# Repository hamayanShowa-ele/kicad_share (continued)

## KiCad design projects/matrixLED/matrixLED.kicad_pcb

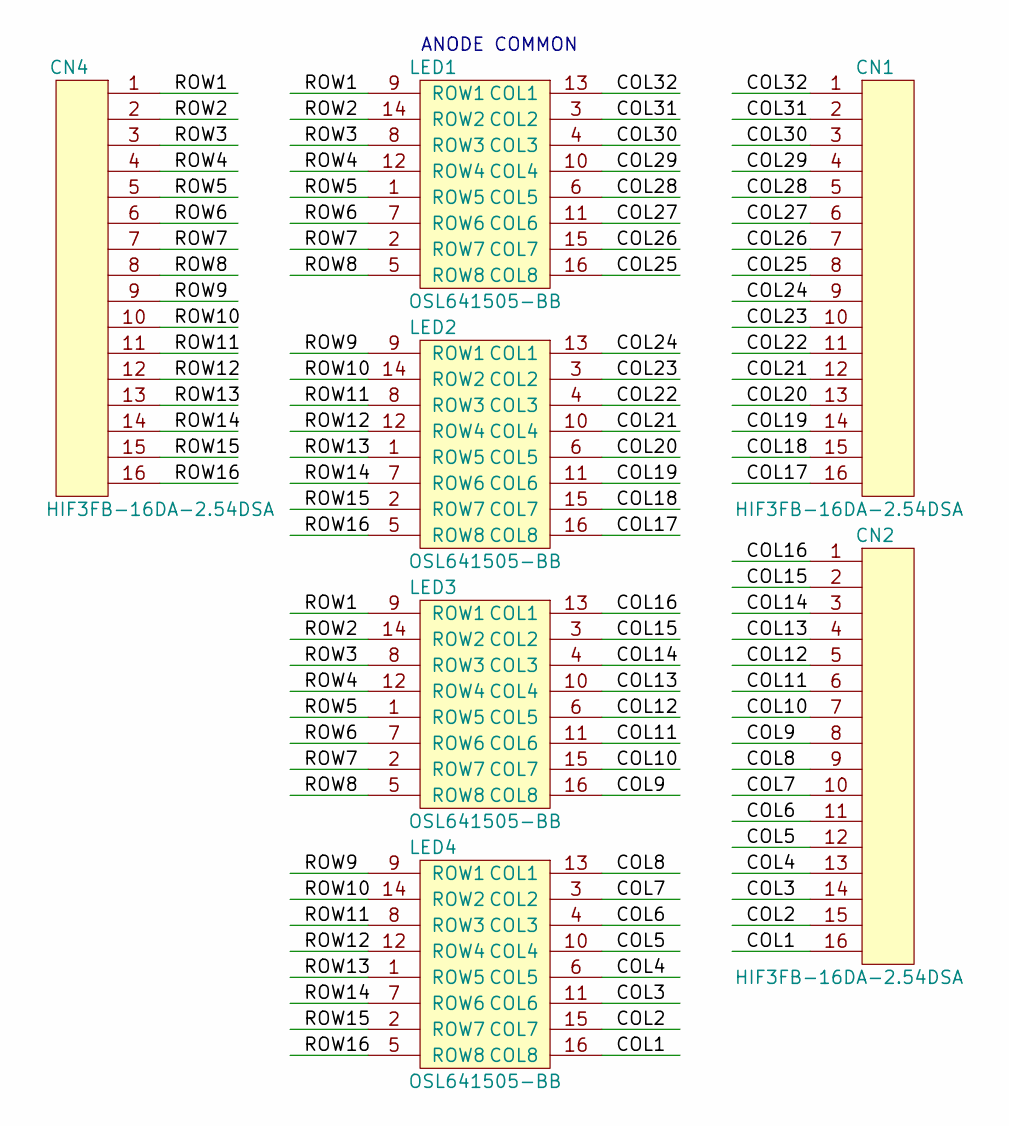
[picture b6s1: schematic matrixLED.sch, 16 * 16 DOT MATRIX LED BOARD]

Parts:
CN1, CN2, CN4: HIF3FB-16DA-2.54DSA; cn_HIF3FC-16PA-254DSA
LED1, LED2, LED3, LED4: OSL641505-BB; led_OSL641505

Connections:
/COL1: CN2.16, LED4.16 (COL8)
/COL2: CN2.15, LED4.15 (COL7)
/COL3: CN2.14, LED4.11 (COL6)
/COL4: CN2.13, LED4.6 (COL5)
/COL5: CN2.12, LED4.10 (COL4)
/COL6: CN2.11, LED4.4 (COL3)
/COL7: CN2.10, LED4.3 (COL2)
/COL8: CN2.9, LED4.13 (COL1)
/COL9: CN2.8, LED3.16 (COL8)
/COL10: CN2.7, LED3.15 (COL7)
/COL11: CN2.6, LED3.11 (COL6)
/COL12: CN2.5, LED3.6 (COL5)
/COL13: CN2.4, LED3.10 (COL4)
/COL14: CN2.3, LED3.4 (COL3)
/COL15: CN2.2, LED3.3 (COL2)
/COL16: CN2.1, LED3.13 (COL1)
/COL17: CN1.16, LED2.16 (COL8)
/COL18: CN1.15, LED2.15 (COL7)
/COL19: CN1.14, LED2.11 (COL6)
/COL20: CN1.13, LED2.6 (COL5)
/COL21: CN1.12, LED2.10 (COL4)
/COL22: CN1.11, LED2.4 (COL3)
/COL23: CN1.10, LED2.3 (COL2)
/COL24: CN1.9, LED2.13 (COL1)
/COL25: CN1.8, LED1.16 (COL8)
/COL26: CN1.7, LED1.15 (COL7)
/COL27: CN1.6, LED1.11 (COL6)
/COL28: CN1.5, LED1.6 (COL5)
/COL29: CN1.4, LED1.10 (COL4)
/COL30: CN1.3, LED1.4 (COL3)
/COL31: CN1.2, LED1.3 (COL2)
/COL32: CN1.1, LED1.13 (COL1)
/ROW1: CN4.1, LED1.9 (ROW1), LED3.9 (ROW1)
/ROW2: CN4.2, LED1.14 (ROW2), LED3.14 (ROW2)
/ROW3: CN4.3, LED1.8 (ROW3), LED3.8 (ROW3)
/ROW4: CN4.4, LED1.12 (ROW4), LED3.12 (ROW4)
/ROW5: CN4.5, LED1.1 (ROW5), LED3.1 (ROW5)
/ROW6: CN4.6, LED1.7 (ROW6), LED3.7 (ROW6)
/ROW7: CN4.7, LED1.2 (ROW7), LED3.2 (ROW7)
/ROW8: CN4.8, LED1.5 (ROW8), LED3.5 (ROW8)
/ROW9: CN4.9, LED2.9 (ROW1), LED4.9 (ROW1)
/ROW10: CN4.10, LED2.14 (ROW2), LED4.14 (ROW2)
/ROW11: CN4.11, LED2.8 (ROW3), LED4.8 (ROW3)
/ROW12: CN4.12, LED2.12 (ROW4), LED4.12 (ROW4)
/ROW13: CN4.13, LED2.1 (ROW5), LED4.1 (ROW5)
/ROW14: CN4.14, LED2.7 (ROW6), LED4.7 (ROW6)
/ROW15: CN4.15, LED2.2 (ROW7), LED4.2 (ROW7)
/ROW16: CN4.16, LED2.5 (ROW8), LED4.5 (ROW8)

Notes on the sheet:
ANODE COMMON

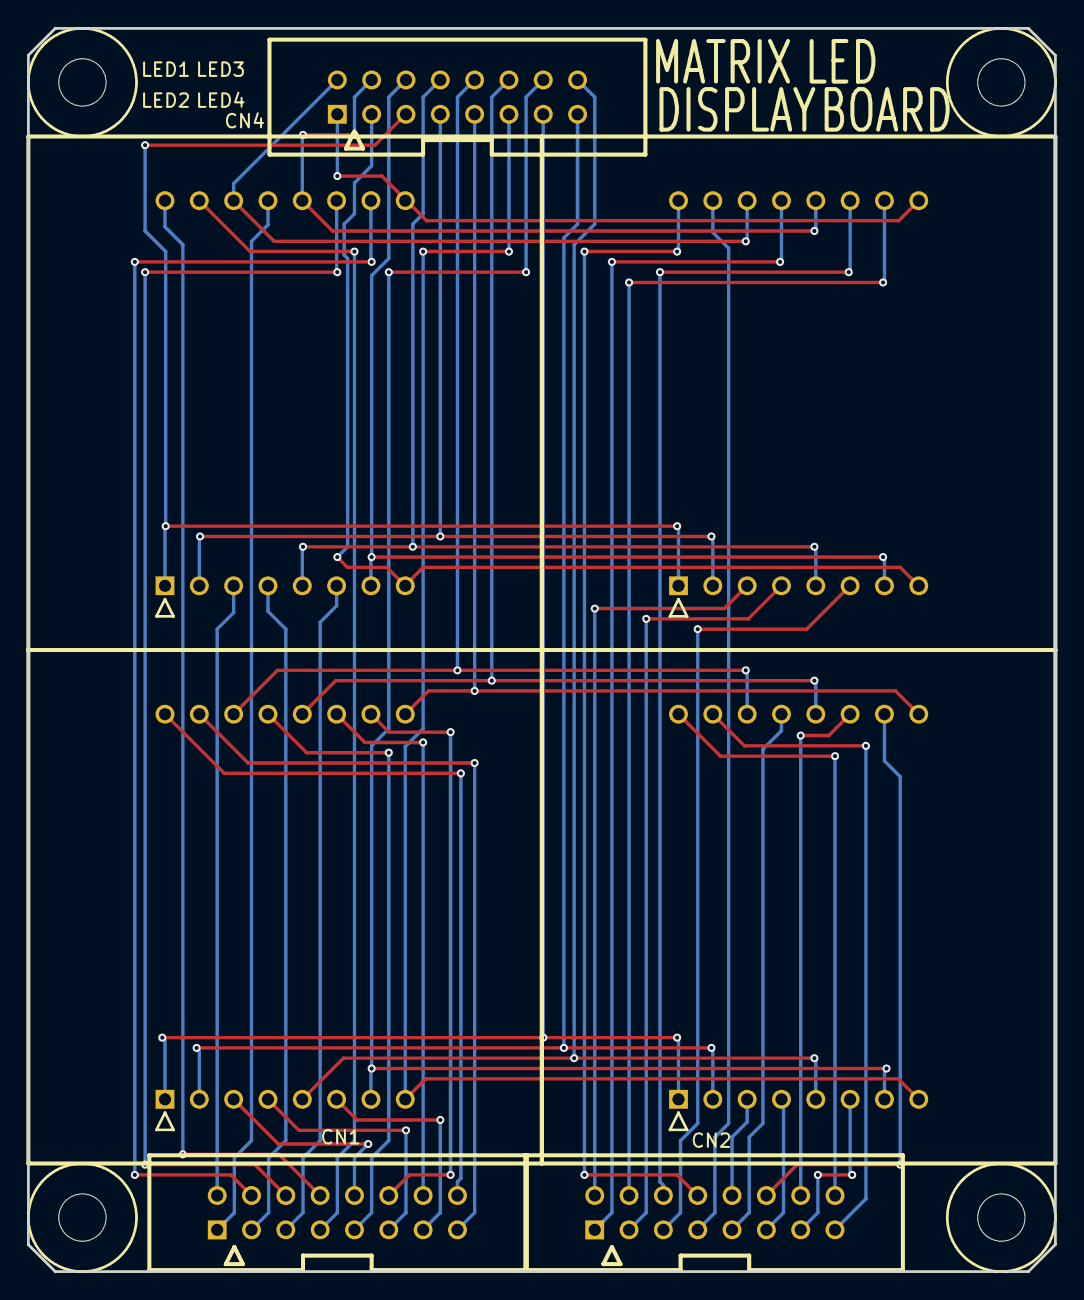
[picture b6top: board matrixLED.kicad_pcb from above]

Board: 2 copper layers, 76.0 x 92.0 mm, 7 parts (0 on the bottom side), 48 nets.

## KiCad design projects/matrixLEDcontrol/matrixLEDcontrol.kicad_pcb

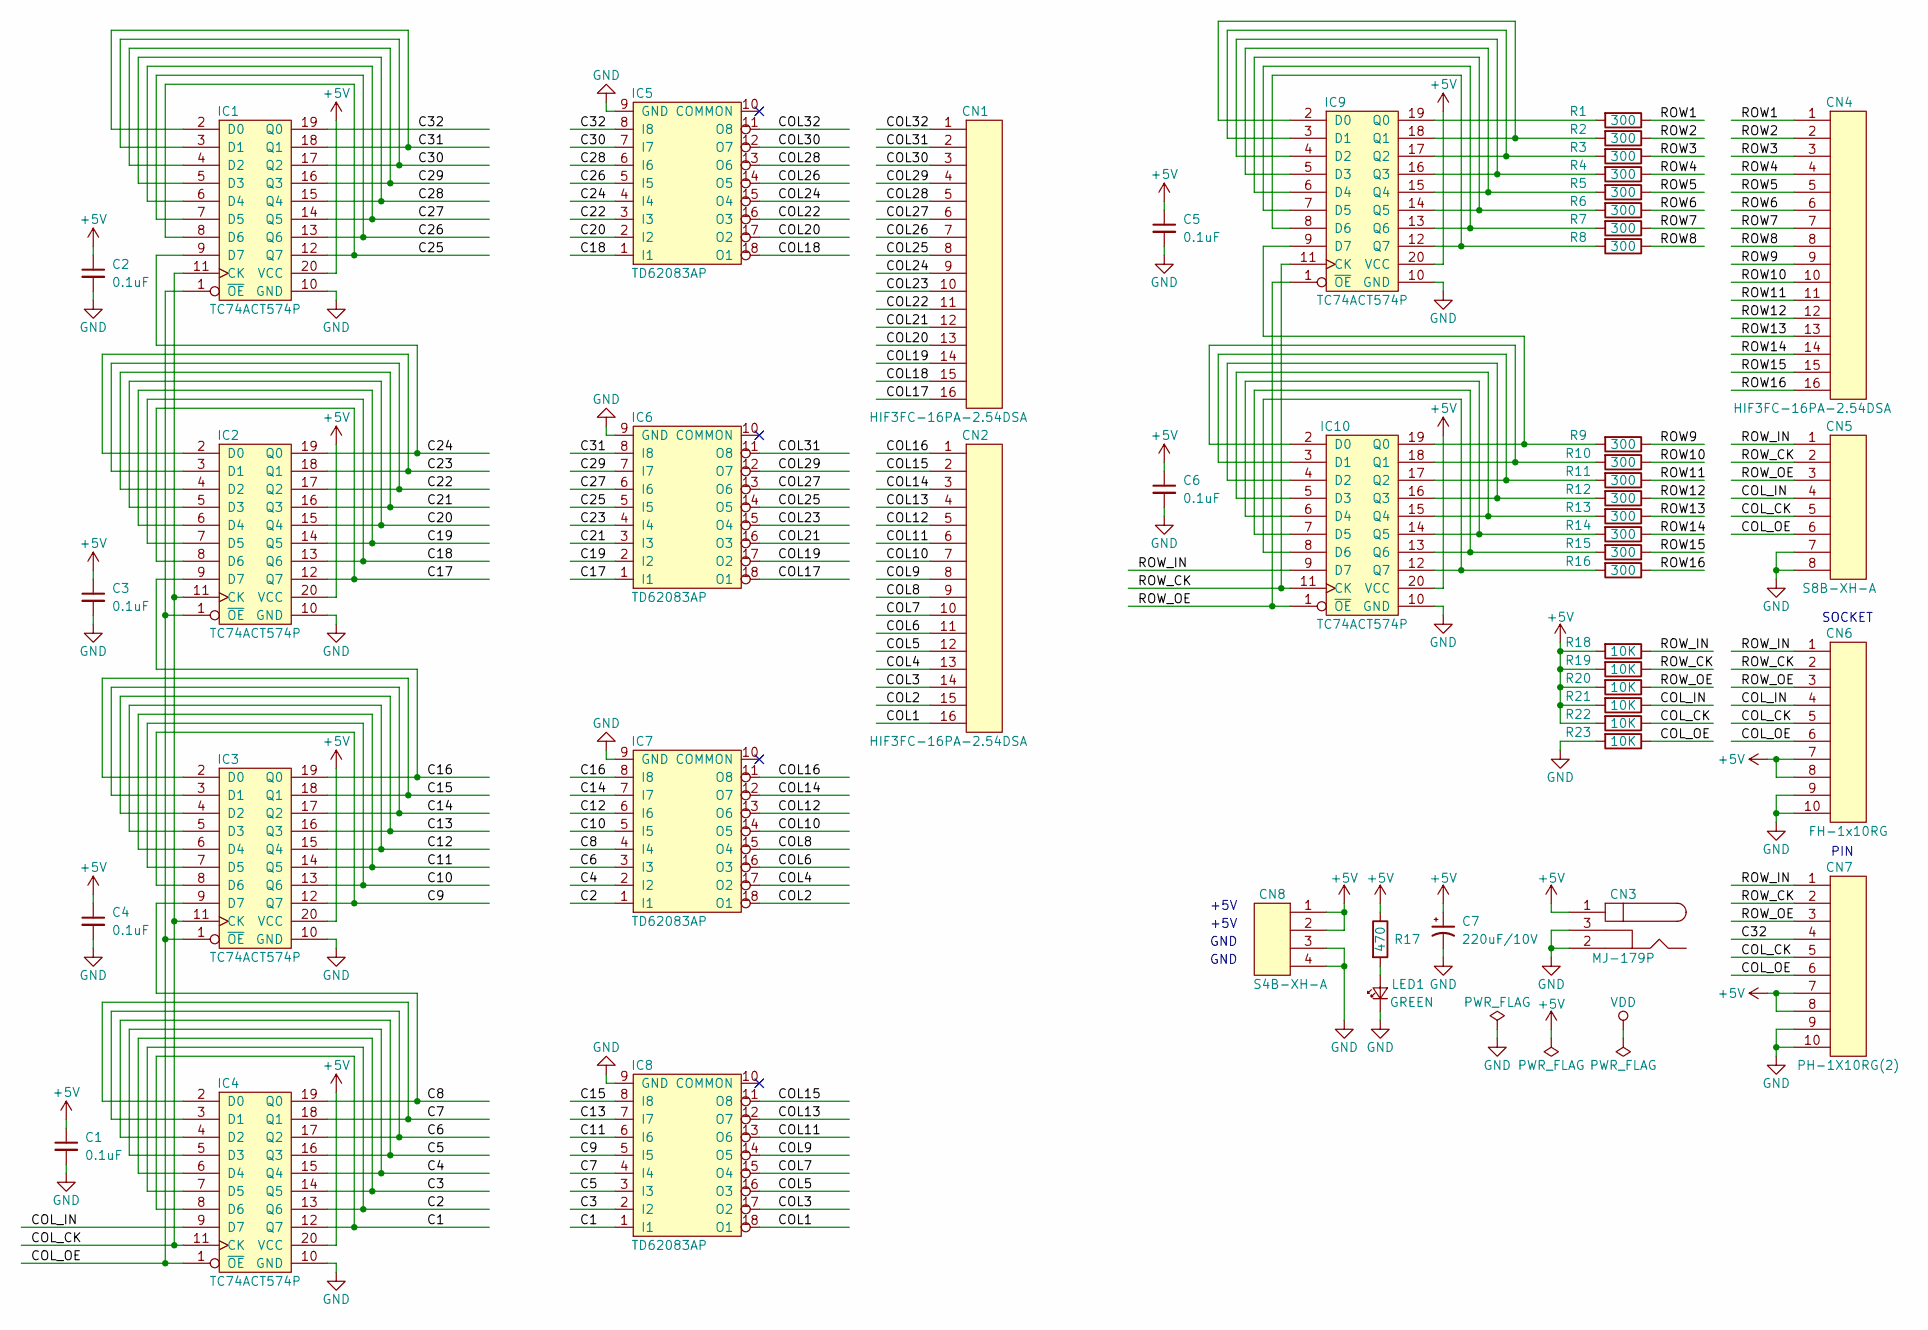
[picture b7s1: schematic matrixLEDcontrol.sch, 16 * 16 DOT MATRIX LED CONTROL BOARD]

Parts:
C1, C2, C3, C4, C5, C6: 0.1uF; C_0805
C7: 220uF/10V; CP_Radial_D8.25mm_P3.80mm
CN1, CN2, CN4: HIF3FC-16PA-2.54DSA; cn_HIF3FC-16PA-254DSA
CN3: MJ-179P
CN5: S8B-XH-A; cn_S8B-XH-A
CN6: FH-1x10RG; cn_FH-1x10RG
CN7: PH-1X10RG(2); cn_PH-1X10RG_2
CN8: S4B-XH-A
IC1, IC2, IC3, IC4, IC9, IC10: TC74ACT574P; ic_DIP-20_W7.62mm
IC5, IC6, IC7, IC8: TD62083AP; ic_DIP-18_W7.62mm
LED1: GREEN; C_0805
R1, R2, R3, R4, R5, R6, R7, R8, R9, R10, R11, R12, R13, R14, R15, R16: 300; C_0805
R17: 470; C_0805
R18, R19, R20, R21, R22, R23: 10K; C_0805

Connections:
+5V: C1.1, C2.1, C3.1, C4.1, C5.1, C6.1, C7.1, CN3.1, CN6.7, CN6.8, CN7.7, CN7.8, CN8.1, CN8.2, IC1.20 (VCC), IC2.20 (VCC), IC3.20 (VCC), IC4.20 (VCC), IC9.20 (VCC), IC10.20 (VCC), R17.1, R18.2, R19.2, R20.2, R21.2, R22.2
/C1: IC4.8 (D6), IC4.12 (Q7), IC8.1 (I1)
/C2: IC4.7 (D5), IC4.13 (Q6), IC7.1 (I1)
/C3: IC4.6 (D4), IC4.14 (Q5), IC8.2 (I2)
/C4: IC4.5 (D3), IC4.15 (Q4), IC7.2 (I2)
/C5: IC4.4 (D2), IC4.16 (Q3), IC8.3 (I3)
/C6: IC4.3 (D1), IC4.17 (Q2), IC7.3 (I3)
/C7: IC4.2 (D0), IC4.18 (Q1), IC8.4 (I4)
/C8: IC3.9 (D7), IC4.19 (Q0), IC7.4 (I4)
/C9: IC3.8 (D6), IC3.12 (Q7), IC8.5 (I5)
/C10: IC3.7 (D5), IC3.13 (Q6), IC7.5 (I5)
/C11: IC3.6 (D4), IC3.14 (Q5), IC8.6 (I6)
/C12: IC3.5 (D3), IC3.15 (Q4), IC7.6 (I6)
/C13: IC3.4 (D2), IC3.16 (Q3), IC8.7 (I7)
/C14: IC3.3 (D1), IC3.17 (Q2), IC7.7 (I7)
/C15: IC3.2 (D0), IC3.18 (Q1), IC8.8 (I8)
/C16: IC2.9 (D7), IC3.19 (Q0), IC7.8 (I8)
/C17: IC2.8 (D6), IC2.12 (Q7), IC6.1 (I1)
/C18: IC2.7 (D5), IC2.13 (Q6), IC5.1 (I1)
/C19: IC2.6 (D4), IC2.14 (Q5), IC6.2 (I2)
/C20: IC2.5 (D3), IC2.15 (Q4), IC5.2 (I2)
/C21: IC2.4 (D2), IC2.16 (Q3), IC6.3 (I3)
/C22: IC2.3 (D1), IC2.17 (Q2), IC5.3 (I3)
/C23: IC2.2 (D0), IC2.18 (Q1), IC6.4 (I4)
/C24: IC1.9 (D7), IC2.19 (Q0), IC5.4 (I4)
/C25: IC1.8 (D6), IC1.12 (Q7), IC6.5 (I5)
/C26: IC1.7 (D5), IC1.13 (Q6), IC5.5 (I5)
/C27: IC1.6 (D4), IC1.14 (Q5), IC6.6 (I6)
/C28: IC1.5 (D3), IC1.15 (Q4), IC5.6 (I6)
/C29: IC1.4 (D2), IC1.16 (Q3), IC6.7 (I7)
/C30: IC1.3 (D1), IC1.17 (Q2), IC5.7 (I7)
/C31: IC1.2 (D0), IC1.18 (Q1), IC6.8 (I8)
/C32: CN7.4, IC1.19 (Q0), IC5.8 (I8)
/COL1: CN2.16, IC8.18 (O1)
/COL2: CN2.15, IC7.18 (O1)
/COL3: CN2.14, IC8.17 (O2)
/COL4: CN2.13, IC7.17 (O2)
/COL5: CN2.12, IC8.16 (O3)
/COL6: CN2.11, IC7.16 (O3)
/COL7: CN2.10, IC8.15 (O4)
/COL8: CN2.9, IC7.15 (O4)
/COL9: CN2.8, IC8.14 (O5)
/COL10: CN2.7, IC7.14 (O5)
/COL11: CN2.6, IC8.13 (O6)
/COL12: CN2.5, IC7.13 (O6)
/COL13: CN2.4, IC8.12 (O7)
/COL14: CN2.3, IC7.12 (O7)
/COL15: CN2.2, IC8.11 (O8)
/COL16: CN2.1, IC7.11 (O8)
/COL17: CN1.16, IC6.18 (O1)
/COL18: CN1.15, IC5.18 (O1)
/COL19: CN1.14, IC6.17 (O2)
/COL20: CN1.13, IC5.17 (O2)
/COL21: CN1.12, IC6.16 (O3)
/COL22: CN1.11, IC5.16 (O3)
/COL23: CN1.10, IC6.15 (O4)
/COL24: CN1.9, IC5.15 (O4)
/COL25: CN1.8, IC6.14 (O5)
/COL26: CN1.7, IC5.14 (O5)
/COL27: CN1.6, IC6.13 (O6)
/COL28: CN1.5, IC5.13 (O6)
/COL29: CN1.4, IC6.12 (O7)
/COL30: CN1.3, IC5.12 (O7)
/COL31: CN1.2, IC6.11 (O8)
/COL32: CN1.1, IC5.11 (O8)
/COL_CK: CN5.5, CN6.5, CN7.5, IC1.11 (CK), IC2.11 (CK), IC3.11 (CK), IC4.11 (CK), R22.1
/COL_IN: CN5.4, CN6.4, IC4.9 (D7), R21.1
/COL_OE: CN5.6, CN6.6, CN7.6, IC1.1 (~OE), IC2.1 (~OE), IC3.1 (~OE), IC4.1 (~OE), R23.1
/ROW1: CN4.1, R1.1
/ROW2: CN4.2, R2.1
/ROW3: CN4.3, R3.1
/ROW4: CN4.4, R4.1
/ROW5: CN4.5, R5.1
/ROW6: CN4.6, R6.1
/ROW7: CN4.7, R7.1
/ROW8: CN4.8, R8.1
/ROW9: CN4.9, R9.1
/ROW10: CN4.10, R10.1
/ROW11: CN4.11, R11.1
/ROW12: CN4.12, R12.1
/ROW13: CN4.13, R13.1
/ROW14: CN4.14, R14.1
/ROW15: CN4.15, R15.1
/ROW16: CN4.16, R16.1
/ROW_CK: CN5.2, CN6.2, CN7.2, IC9.11 (CK), IC10.11 (CK), R19.1
/ROW_IN: CN5.1, CN6.1, CN7.1, IC10.9 (D7), R18.1
/ROW_OE: CN5.3, CN6.3, CN7.3, IC9.1 (~OE), IC10.1 (~OE), R20.1
GND: C1.2, C2.2, C3.2, C4.2, C5.2, C6.2, C7.2, CN3.2, CN3.3, CN5.7, CN5.8, CN6.9, CN6.10, CN7.9, CN7.10, CN8.3, CN8.4, IC1.10 (GND), IC2.10 (GND), IC3.10 (GND), IC4.10 (GND), IC5.9 (GND), IC6.9 (GND), IC7.9 (GND), IC8.9 (GND), IC9.10 (GND), IC10.10 (GND), LED1.2 (K), R23.2
unnamed: IC9.8 (D6), IC9.12 (Q7), R8.2
unnamed: IC9.7 (D5), IC9.13 (Q6), R7.2
unnamed: IC9.6 (D4), IC9.14 (Q5), R6.2
unnamed: IC9.5 (D3), IC9.15 (Q4), R5.2
unnamed: IC9.4 (D2), IC9.16 (Q3), R4.2
unnamed: IC9.3 (D1), IC9.17 (Q2), R3.2
unnamed: IC9.2 (D0), IC9.18 (Q1), R2.2
unnamed: IC9.19 (Q0), R1.2
unnamed: IC10.8 (D6), IC10.12 (Q7), R16.2
unnamed: IC10.7 (D5), IC10.13 (Q6), R15.2
unnamed: IC10.6 (D4), IC10.14 (Q5), R14.2
unnamed: IC10.5 (D3), IC10.15 (Q4), R13.2
unnamed: IC10.4 (D2), IC10.16 (Q3), R12.2
unnamed: IC10.3 (D1), IC10.17 (Q2), R11.2
unnamed: IC10.2 (D0), IC10.18 (Q1), R10.2
unnamed: IC9.9 (D7), IC10.19 (Q0), R9.2
unnamed: LED1.1 (A), R17.2

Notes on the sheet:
SOCKET
PIN
+5V
GND

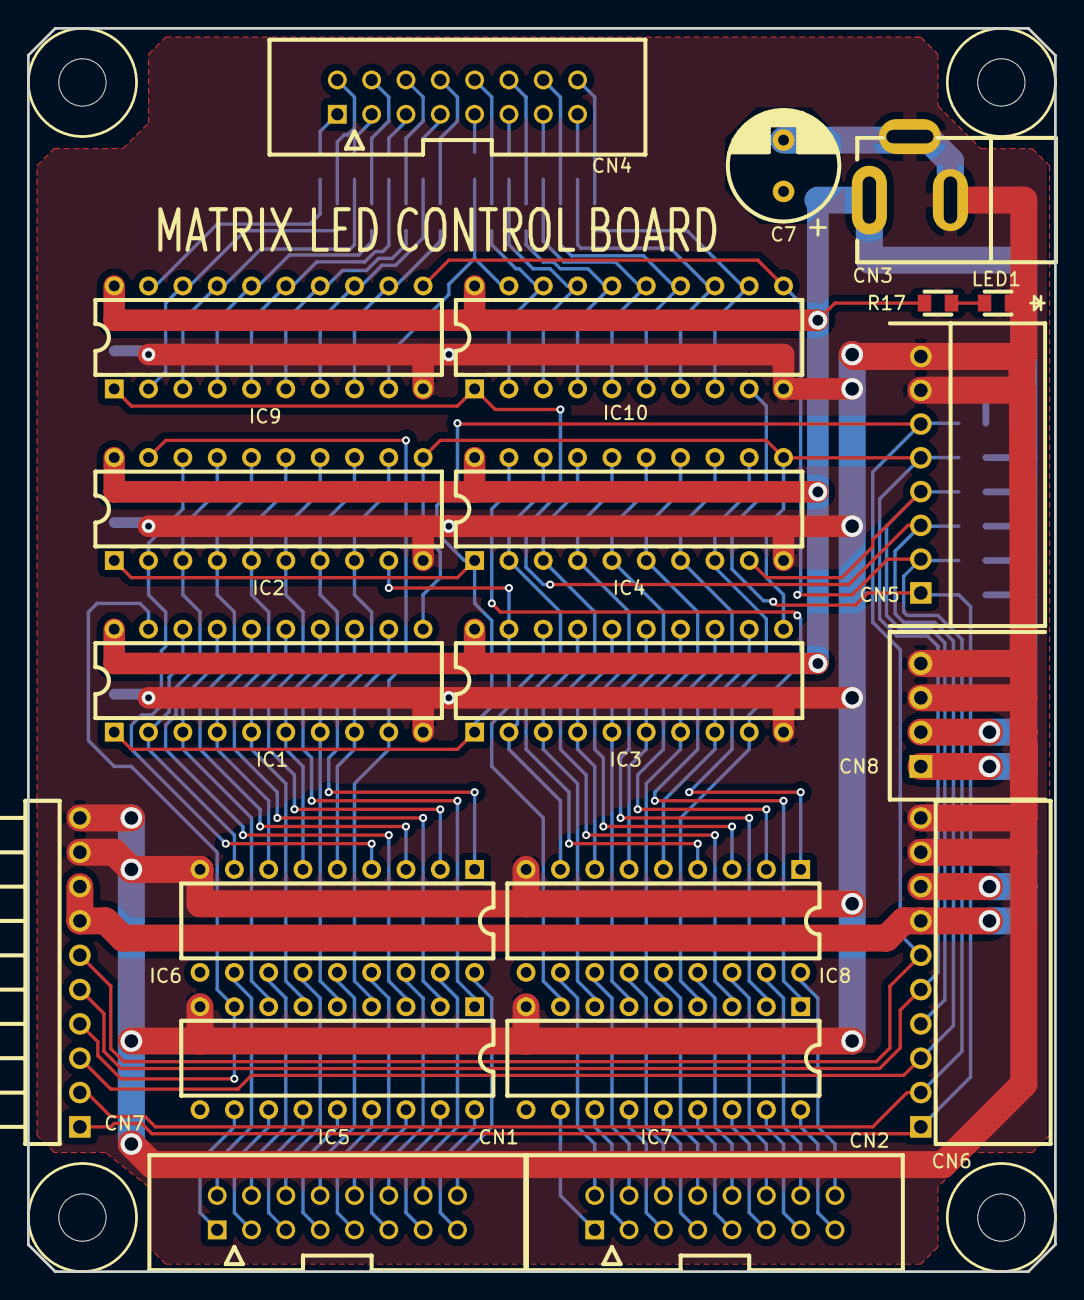
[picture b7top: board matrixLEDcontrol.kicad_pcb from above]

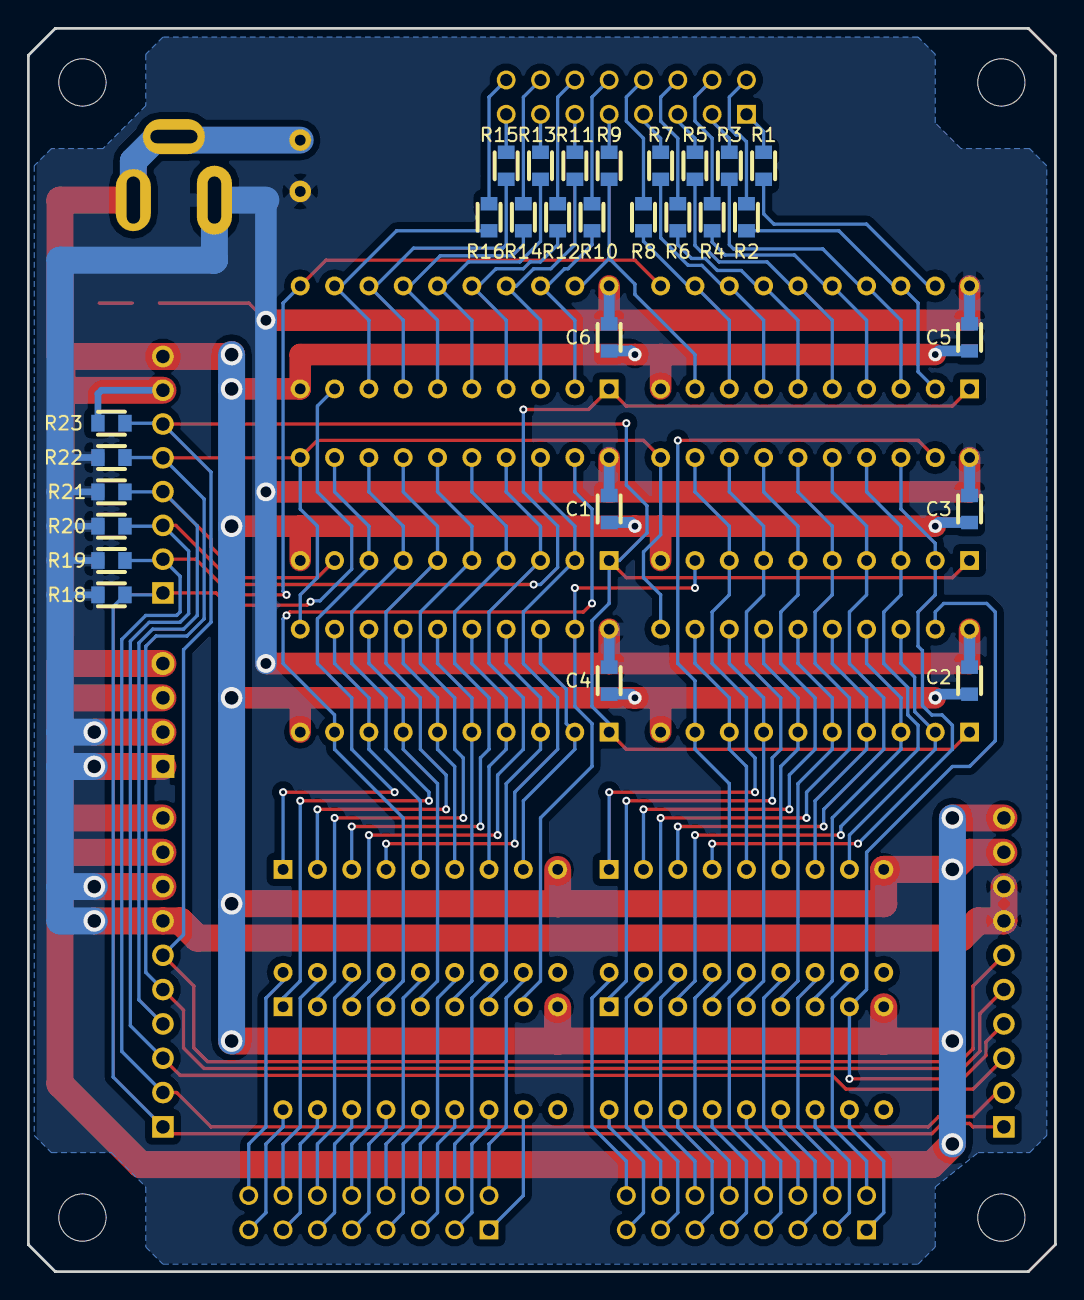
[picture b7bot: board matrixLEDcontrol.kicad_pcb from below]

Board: 2 copper layers, 76.0 x 92.0 mm, 49 parts (28 on the bottom side), 105 nets.

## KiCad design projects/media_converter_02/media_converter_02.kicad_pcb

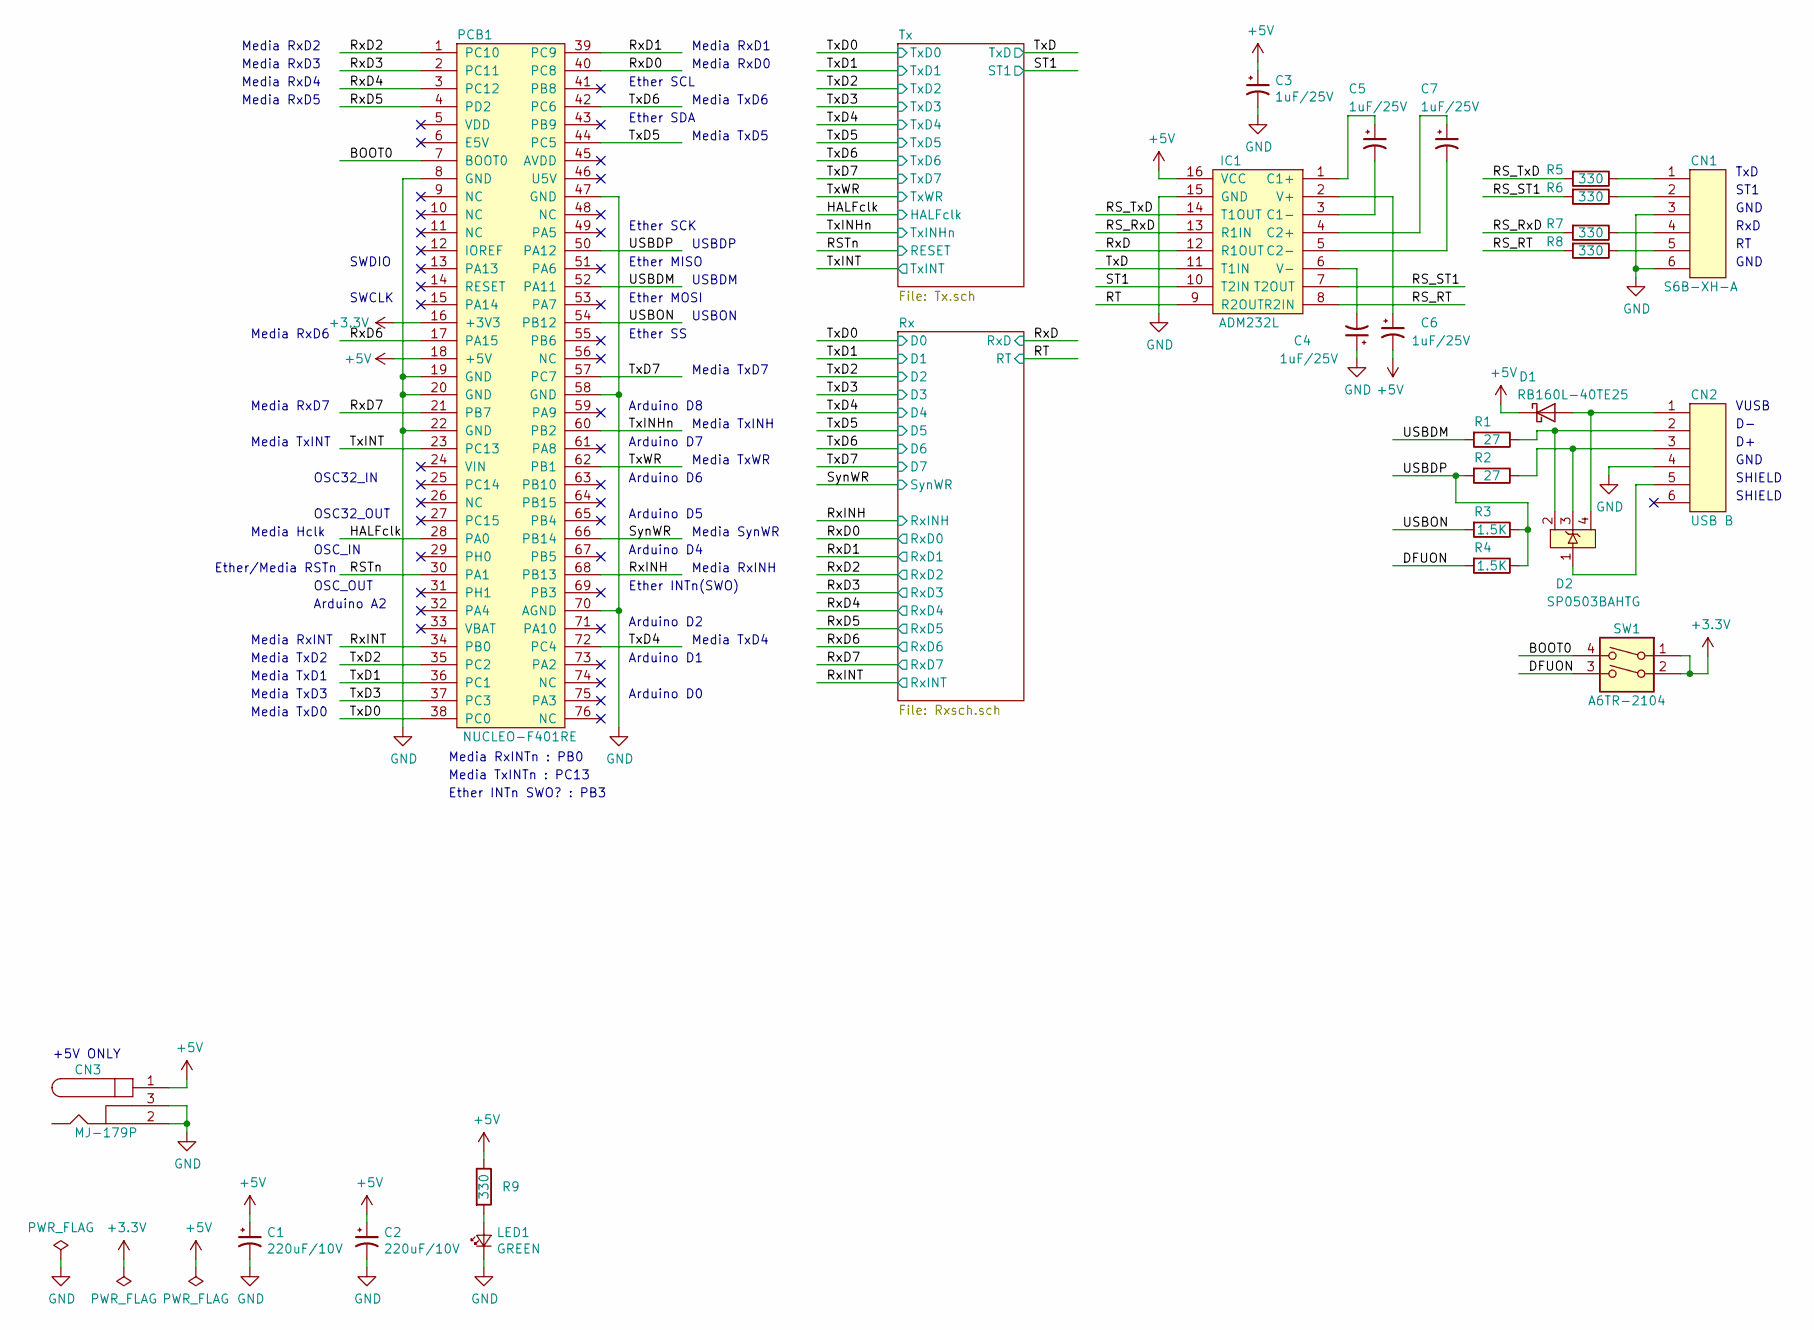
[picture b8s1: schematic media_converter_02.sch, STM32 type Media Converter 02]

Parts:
C1, C2: 220uF/10V; CP_Radial_D8.25mm_P3.80mm
C3, C4, C5, C6, C7: 1uF/25V; CP_D3R5_P2R5
CN1: S6B-XH-A; cn_S6B-XH-A
CN2: USB B; cn_USB_B
CN3: MJ-179P; cn_MJ-179P
D1: RB160L-40TE25; d_SX34F
D2: SP0503BAHTG; d_SP0503BAHT
IC1: ADM232L; ic_DIP-16_W7.62mm
LED1: GREEN; LED_D3.0mm
PCB1: NUCLEO-F401RE; pcb_Nucleo_Extension_001
R1, R2: 27; C_0603
R3, R4: 1.5K; C_0603
R5, R6, R7, R8, R9: 330; C_0603
SW1: A6TR-2104; sw_A6TR-2104

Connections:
+3V3: PCB1.16 (+3V3), SW1.1, SW1.2
+5V: C1.1, C2.1, C3.1, C6.2, CN3.1, D1.2 (K), IC1.16 (VCC), PCB1.18 (+5V), R9.1; also elsewhere on the board
/BOOT0: PCB1.7 (BOOT0), SW1.4
/DFUON: R4.2, SW1.3
/HALFclk: PCB1.28 (PA0); also elsewhere on the board
/RSTn: PCB1.30 (PA1); also elsewhere on the board
/RS_RT: IC1.8 (R2IN), R8.2
/RS_RxD: IC1.13 (R1IN), R7.2
/RS_ST1: IC1.7 (T2OUT), R6.2
/RS_TxD: IC1.14 (T1OUT), R5.2
/RT: IC1.9 (R2OUT); also elsewhere on the board
/RxD: IC1.12 (R1OUT); also elsewhere on the board
/RxD0: PCB1.40 (PC8); also elsewhere on the board
/RxD1: PCB1.39 (PC9); also elsewhere on the board
/RxD2: PCB1.1 (PC10); also elsewhere on the board
/RxD3: PCB1.2 (PC11); also elsewhere on the board
/RxD4: PCB1.3 (PC12); also elsewhere on the board
/RxD5: PCB1.4 (PD2); also elsewhere on the board
/RxD6: PCB1.17 (PA15); also elsewhere on the board
/RxD7: PCB1.21 (PB7); also elsewhere on the board
/RxINH: PCB1.68 (PB13); also elsewhere on the board
/RxINT: PCB1.34 (PB0); also elsewhere on the board
/ST1: IC1.10 (T2IN); also elsewhere on the board
/SynWR: PCB1.66 (PB14); also elsewhere on the board
/TxD: IC1.11 (T1IN); also elsewhere on the board
/TxD0: PCB1.38 (PC0); also elsewhere on the board
/TxD1: PCB1.36 (PC1); also elsewhere on the board
/TxD2: PCB1.35 (PC2); also elsewhere on the board
/TxD3: PCB1.37 (PC3); also elsewhere on the board
/TxD4: PCB1.72 (PC4); also elsewhere on the board
/TxD5: PCB1.44 (PC5); also elsewhere on the board
/TxD6: PCB1.42 (PC6); also elsewhere on the board
/TxD7: PCB1.57 (PC7); also elsewhere on the board
/TxINHn: PCB1.60 (PB2); also elsewhere on the board
/TxINT: PCB1.23 (PC13); also elsewhere on the board
/TxWR: PCB1.62 (PB1); also elsewhere on the board
/USBDM: PCB1.52 (PA11), R1.2
/USBDP: PCB1.50 (PA12), R2.2, R3.1, R4.1
/USBON: PCB1.54 (PB12), R3.2
GND: C1.2, C2.2, C3.2, C4.1, CN1.3, CN1.6, CN2.4, CN3.2, CN3.3, IC1.15 (GND), LED1.2 (K), PCB1.8 (GND), PCB1.19 (GND), PCB1.20 (GND), PCB1.22 (GND), PCB1.47 (GND), PCB1.58 (GND), PCB1.70 (AGND); also elsewhere on the board
unnamed: C4.2, IC1.6 (V-)
unnamed: C5.1, IC1.1 (C1+)
unnamed: C5.2, IC1.3 (C1-)
unnamed: C6.1, IC1.2 (V+)
unnamed: C7.1, IC1.4 (C2+)
unnamed: C7.2, IC1.5 (C2-)
unnamed: CN1.1, R5.1
unnamed: CN1.2, R6.1
unnamed: CN1.4, R7.1
unnamed: CN1.5, R8.1
unnamed: CN2.1, D1.1 (A), D2.4
unnamed: CN2.2, D2.2, R1.1
unnamed: CN2.3, D2.3, R2.1
unnamed: CN2.5, D2.1
unnamed: LED1.1 (A), R9.2

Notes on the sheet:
Ether/Media RSTn
Ether MOSI
Ether MISO
Ether SCK
Ether INTn(SWO)
Ether SS
Ether SCL
Ether SDA
Media TxD7
Media TxD6
Media TxD5
Media TxD4
Media TxD3
Media TxD2
Media TxD1
Media TxD0
Media TxWR
Media Hclk
Media TxINH
Media RxD0
Media RxD1
Media RxD2
Media RxD3
Media RxD4
Media RxD5
Media RxD6
Media RxD7
Media SynWR
Media RxINH
OSC_OUT
OSC_IN
Media RxINTn : PB0
Media TxINTn : PC13
Ether INTn SWO? : PB3
SWDIO
SWCLK
USBDP
USBDM
USBON
OSC32_IN

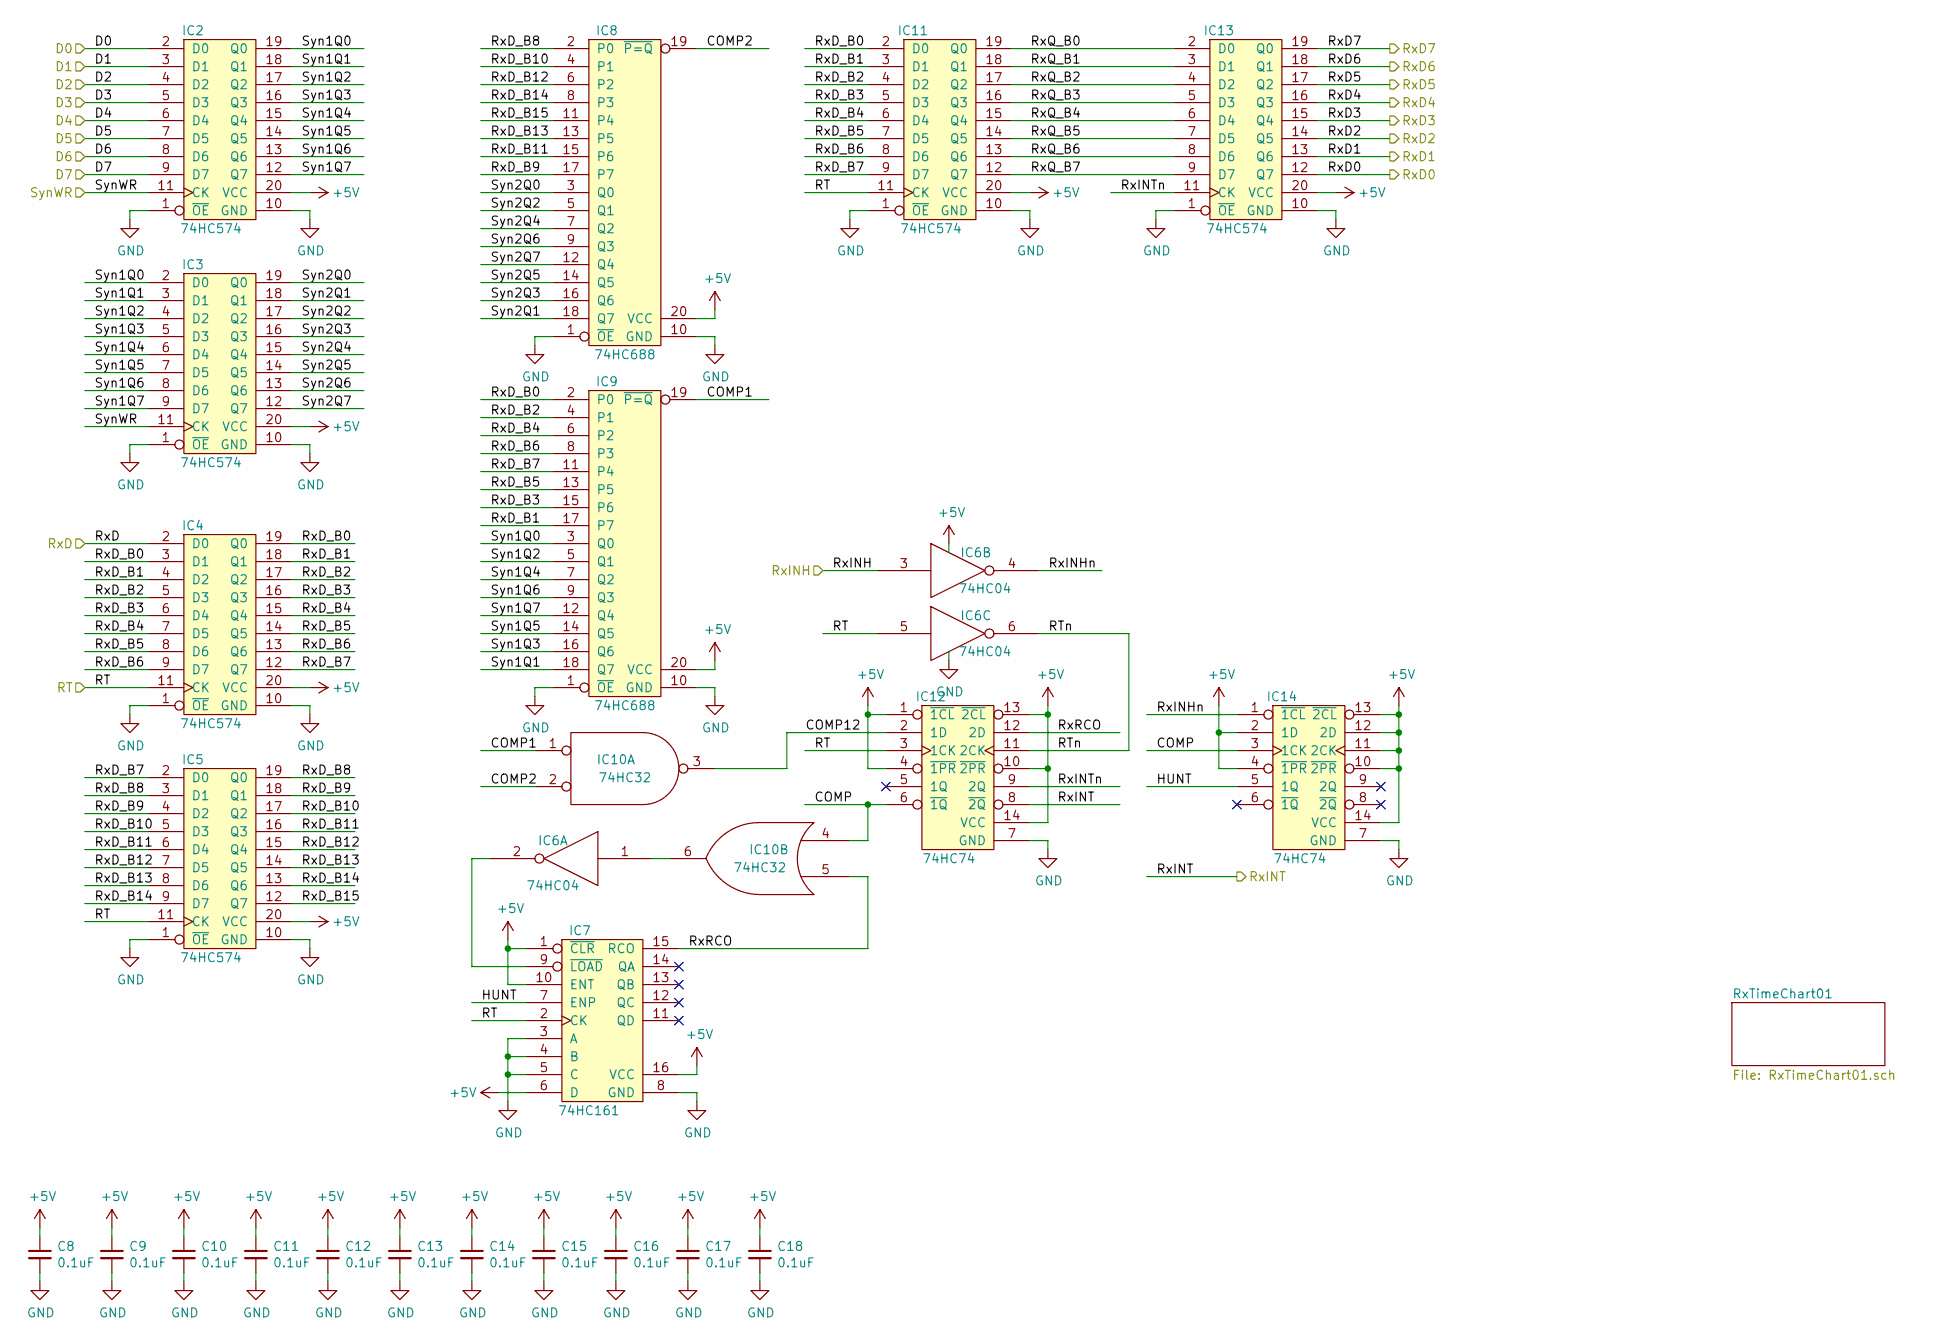
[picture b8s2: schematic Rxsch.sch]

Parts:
C8, C9, C10, C11, C12, C13, C14, C15, C16, C17, C18: 0.1uF; C_0603
IC2, IC3, IC4, IC5, IC11, IC13: 74HC574; ic_DIP-20_W7.62mm
IC6: 74HC04; IC_DIP-14_W7.62mm
IC7: 74HC161; ic_DIP-16_W7.62mm
IC8, IC9: 74HC688; ic_DIP-20_W7.62mm
IC10: 74HC32; IC_DIP-14_W7.62mm
IC12, IC14: 74HC74; IC_DIP-14_W7.62mm

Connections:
+5V: C8.1, C9.1, C10.1, C11.1, C12.1, C13.1, C14.1, C15.1, C16.1, C17.1, C18.1, IC2.20 (VCC), IC3.20 (VCC), IC4.20 (VCC), IC5.20 (VCC), IC6.14 (VCC), IC7.1 (~CLR), IC7.6 (D), IC7.10 (ENT), IC7.16 (VCC), IC8.20 (VCC), IC9.20 (VCC), IC10.14 (VCC), IC11.20 (VCC), IC12.1 (~1CL), IC12.4 (~1PR), IC12.10 (~2PR), IC12.13 (~2CL), IC12.14 (VCC), IC13.20 (VCC), IC14.2 (1D), IC14.4 (~1PR), IC14.10 (~2PR), IC14.11 (2CK), IC14.12 (2D), IC14.13 (~2CL), IC14.14 (VCC); also elsewhere on the board
/RT: IC4.11 (CK), IC5.11 (CK), IC6.5, IC7.2 (CK), IC11.11 (CK), IC12.3 (1CK); also elsewhere on the board
/Rx/COMP: IC10.4, IC12.6 (~1Q), IC14.3 (1CK)
/Rx/COMP1: IC9.19 (~P=Q), IC10.1
/Rx/COMP2: IC8.19 (~P=Q), IC10.2
/Rx/COMP12: IC10.3, IC12.2 (1D)
/Rx/HUNT: IC7.7 (ENP), IC14.5 (1Q)
/Rx/RTn: IC6.6, IC12.11 (2CK)
/Rx/RxD_B0: IC4.3 (D1), IC4.19 (Q0), IC9.2 (P0), IC11.2 (D0)
/Rx/RxD_B1: IC4.4 (D2), IC4.18 (Q1), IC9.17 (P7), IC11.3 (D1)
/Rx/RxD_B2: IC4.5 (D3), IC4.17 (Q2), IC9.4 (P1), IC11.4 (D2)
/Rx/RxD_B3: IC4.6 (D4), IC4.16 (Q3), IC9.15 (P6), IC11.5 (D3)
/Rx/RxD_B4: IC4.7 (D5), IC4.15 (Q4), IC9.6 (P2), IC11.6 (D4)
/Rx/RxD_B5: IC4.8 (D6), IC4.14 (Q5), IC9.13 (P5), IC11.7 (D5)
/Rx/RxD_B6: IC4.9 (D7), IC4.13 (Q6), IC9.8 (P3), IC11.8 (D6)
/Rx/RxD_B7: IC4.12 (Q7), IC5.2 (D0), IC9.11 (P4), IC11.9 (D7)
/Rx/RxD_B8: IC5.3 (D1), IC5.19 (Q0), IC8.2 (P0)
/Rx/RxD_B9: IC5.4 (D2), IC5.18 (Q1), IC8.17 (P7)
/Rx/RxD_B10: IC5.5 (D3), IC5.17 (Q2), IC8.4 (P1)
/Rx/RxD_B11: IC5.6 (D4), IC5.16 (Q3), IC8.15 (P6)
/Rx/RxD_B12: IC5.7 (D5), IC5.15 (Q4), IC8.6 (P2)
/Rx/RxD_B13: IC5.8 (D6), IC5.14 (Q5), IC8.13 (P5)
/Rx/RxD_B14: IC5.9 (D7), IC5.13 (Q6), IC8.8 (P3)
/Rx/RxD_B15: IC5.12 (Q7), IC8.11 (P4)
/Rx/RxINHn: IC6.4, IC14.1 (~1CL)
/Rx/RxINTn: IC12.9 (2Q), IC13.11 (CK)
/Rx/RxQ_B0: IC11.19 (Q0), IC13.2 (D0)
/Rx/RxQ_B1: IC11.18 (Q1), IC13.3 (D1)
/Rx/RxQ_B2: IC11.17 (Q2), IC13.4 (D2)
/Rx/RxQ_B3: IC11.16 (Q3), IC13.5 (D3)
/Rx/RxQ_B4: IC11.15 (Q4), IC13.6 (D4)
/Rx/RxQ_B5: IC11.14 (Q5), IC13.7 (D5)
/Rx/RxQ_B6: IC11.13 (Q6), IC13.8 (D6)
/Rx/RxQ_B7: IC11.12 (Q7), IC13.9 (D7)
/Rx/RxRCO: IC7.15 (RCO), IC10.5, IC12.12 (2D)
/Rx/Syn1Q0: IC2.19 (Q0), IC3.2 (D0), IC9.3 (Q0)
/Rx/Syn1Q1: IC2.18 (Q1), IC3.3 (D1), IC9.18 (Q7)
/Rx/Syn1Q2: IC2.17 (Q2), IC3.4 (D2), IC9.5 (Q1)
/Rx/Syn1Q3: IC2.16 (Q3), IC3.5 (D3), IC9.16 (Q6)
/Rx/Syn1Q4: IC2.15 (Q4), IC3.6 (D4), IC9.7 (Q2)
/Rx/Syn1Q5: IC2.14 (Q5), IC3.7 (D5), IC9.14 (Q5)
/Rx/Syn1Q6: IC2.13 (Q6), IC3.8 (D6), IC9.9 (Q3)
/Rx/Syn1Q7: IC2.12 (Q7), IC3.9 (D7), IC9.12 (Q4)
/Rx/Syn2Q0: IC3.19 (Q0), IC8.3 (Q0)
/Rx/Syn2Q1: IC3.18 (Q1), IC8.18 (Q7)
/Rx/Syn2Q2: IC3.17 (Q2), IC8.5 (Q1)
/Rx/Syn2Q3: IC3.16 (Q3), IC8.16 (Q6)
/Rx/Syn2Q4: IC3.15 (Q4), IC8.7 (Q2)
/Rx/Syn2Q5: IC3.14 (Q5), IC8.14 (Q5)
/Rx/Syn2Q6: IC3.13 (Q6), IC8.9 (Q3)
/Rx/Syn2Q7: IC3.12 (Q7), IC8.12 (Q4)
/RxD: IC4.2 (D0); also elsewhere on the board
/RxD0: IC13.12 (Q7); also elsewhere on the board
/RxD1: IC13.13 (Q6); also elsewhere on the board
/RxD2: IC13.14 (Q5); also elsewhere on the board
/RxD3: IC13.15 (Q4); also elsewhere on the board
/RxD4: IC13.16 (Q3); also elsewhere on the board
/RxD5: IC13.17 (Q2); also elsewhere on the board
/RxD6: IC13.18 (Q1); also elsewhere on the board
/RxD7: IC13.19 (Q0); also elsewhere on the board
/RxINH: IC6.3; also elsewhere on the board
/RxINT: IC12.8 (~2Q); also elsewhere on the board
/SynWR: IC2.11 (CK), IC3.11 (CK); also elsewhere on the board
/TxD0: IC2.2 (D0); also elsewhere on the board
/TxD1: IC2.3 (D1); also elsewhere on the board
/TxD2: IC2.4 (D2); also elsewhere on the board
/TxD3: IC2.5 (D3); also elsewhere on the board
/TxD4: IC2.6 (D4); also elsewhere on the board
/TxD5: IC2.7 (D5); also elsewhere on the board
/TxD6: IC2.8 (D6); also elsewhere on the board
/TxD7: IC2.9 (D7); also elsewhere on the board
GND: C8.2, C9.2, C10.2, C11.2, C12.2, C13.2, C14.2, C15.2, C16.2, C17.2, C18.2, IC2.1 (~OE), IC2.10 (GND), IC3.1 (~OE), IC3.10 (GND), IC4.1 (~OE), IC4.10 (GND), IC5.1 (~OE), IC5.10 (GND), IC6.7 (GNDA), IC7.3 (A), IC7.4 (B), IC7.5 (C), IC7.8 (GND), IC8.1 (~OE), IC8.10 (GND), IC9.1 (~OE), IC9.10 (GND), IC10.7 (GND), IC11.1 (~OE), IC11.10 (GND), IC12.7 (GND), IC13.1 (~OE), IC13.10 (GND), IC14.7 (GND); also elsewhere on the board
unnamed: IC6.2, IC7.9 (~LOAD)
unnamed: IC6.1, IC10.6
